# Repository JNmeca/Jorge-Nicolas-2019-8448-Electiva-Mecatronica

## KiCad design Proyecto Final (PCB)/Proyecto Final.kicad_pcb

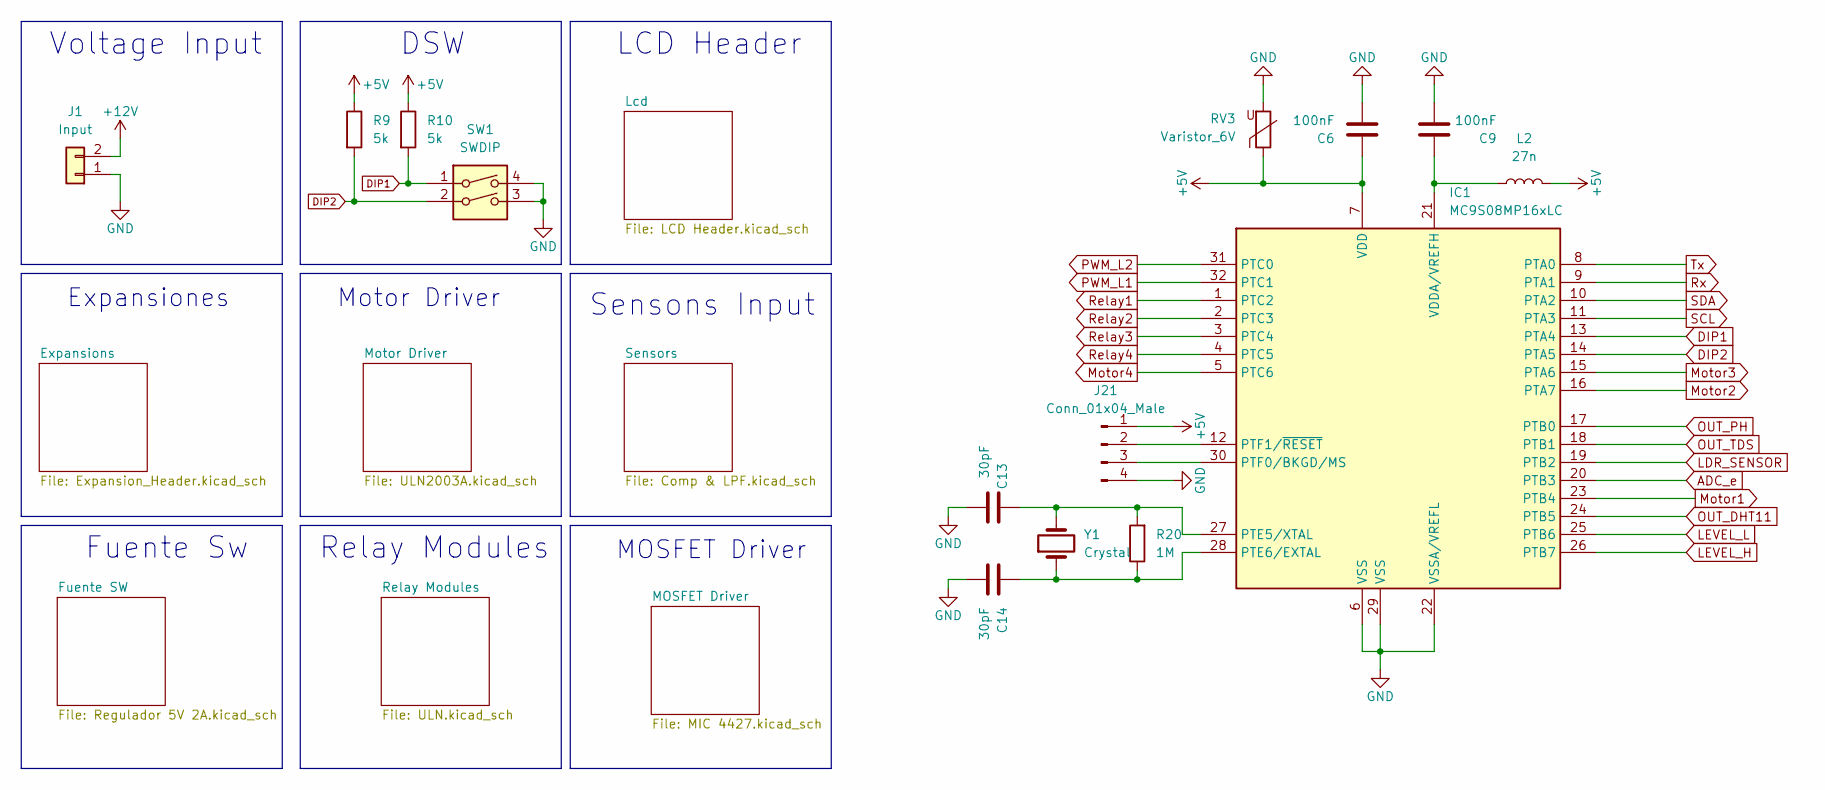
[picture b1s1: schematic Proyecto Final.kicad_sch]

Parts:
C6, C9: 100nF; C_0603_1608Metric
C13, C14: 30pF; C_0603_1608Metric
IC1: MC9S08MP16xLC; LQFP-32_7x7mm_P0.8mm
J1: Input; TerminalBlock_bornier-2_P5.08mm
J21: Conn_01x04_Male; PinHeader_1x04_P2.54mm_Vertical
L2: 27n; L_0805_2012Metric
R9, R10: 5k; R_0603_1608Metric
R20: 1M; R_0201_0603Metric
RV3: Varistor_6V; C_0805_2012Metric
SW1: SWDIP; SW_DIP_SPSTx02_Slide_9.78x7.26mm_W7.62mm_P2.54mm
Y1: Crystal; Crystal_HC49-4H_Vertical

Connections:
+5V: C6.2, IC1.7 (VDD), J21.1, L2.2, R9.1, R10.1, RV3.1; also elsewhere on the board
+12V: J1.2; also elsewhere on the board
ADC_e: IC1.20 (PTB3); also elsewhere on the board
DIP1: IC1.13 (PTA4), R10.2, SW1.1
DIP2: IC1.14 (PTA5), R9.2, SW1.2
GND: C6.1, C9.1, C13.1, C14.1, IC1.6 (VSS), IC1.22 (VSSA/VREFL), IC1.29 (VSS), J1.1, J21.4, RV3.2, SW1.3, SW1.4; also elsewhere on the board
LDR_SENSOR: IC1.19 (PTB2); also elsewhere on the board
LEVEL_H: IC1.26 (PTB7); also elsewhere on the board
LEVEL_L: IC1.25 (PTB6); also elsewhere on the board
Motor1: IC1.23 (PTB4); also elsewhere on the board
Motor2: IC1.16 (PTA7); also elsewhere on the board
Motor3: IC1.15 (PTA6); also elsewhere on the board
Motor4: IC1.5 (PTC6); also elsewhere on the board
unnamed: C9.2, IC1.21 (VDDA/VREFH), L2.1
unnamed: C13.2, IC1.27 (PTE5/XTAL), R20.2, Y1.2
unnamed: C14.2, IC1.28 (PTE6/EXTAL), R20.1, Y1.1
unnamed: IC1.12 (PTF1/~RESET), J21.2
unnamed: IC1.30 (PTF0/BKGD/MS), J21.3
OUT_DHT11: IC1.24 (PTB5); also elsewhere on the board
OUT_PH: IC1.17 (PTB0); also elsewhere on the board
OUT_TDS: IC1.18 (PTB1); also elsewhere on the board
PWM_L1: IC1.32 (PTC1); also elsewhere on the board
PWM_L2: IC1.31 (PTC0); also elsewhere on the board
Relay1: IC1.1 (PTC2); also elsewhere on the board
Relay2: IC1.2 (PTC3); also elsewhere on the board
Relay3: IC1.3 (PTC4); also elsewhere on the board
Relay4: IC1.4 (PTC5); also elsewhere on the board
Rx: IC1.9 (PTA1); also elsewhere on the board
SCL: IC1.11 (PTA3); also elsewhere on the board
SDA: IC1.10 (PTA2); also elsewhere on the board
Tx: IC1.8 (PTA0); also elsewhere on the board

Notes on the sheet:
DSW
Expansiones
LCD Header
Motor Driver
MOSFET Driver
Voltage Input
Sensons Input
Fuente Sw
Relay Modules

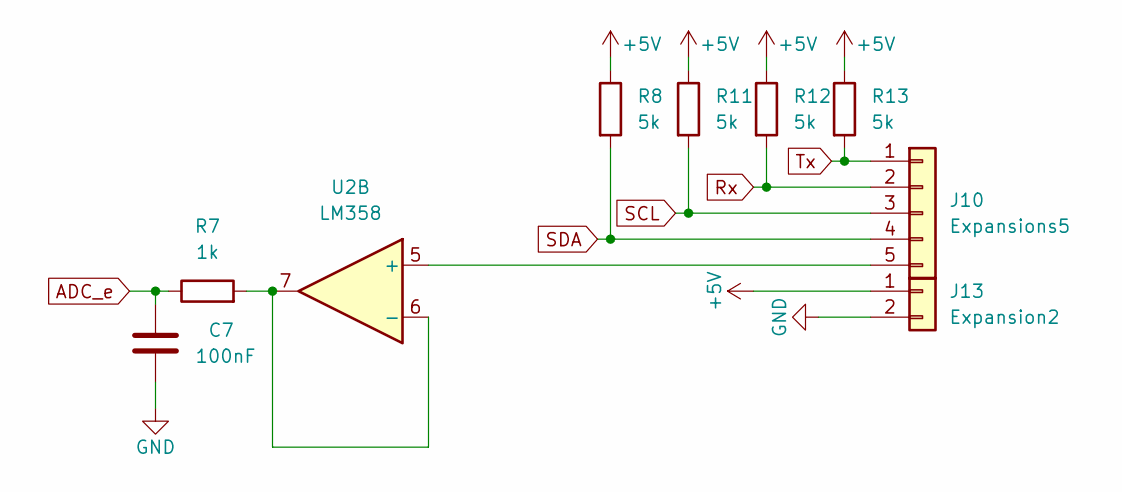
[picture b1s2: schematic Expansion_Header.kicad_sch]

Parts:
C7: 100nF; C_0603_1608Metric
J10: Expansions5; TerminalBlock_bornier-5_P5.08mm
J13: Expansion2; TerminalBlock_bornier-2_P5.08mm
R7: 1k; R_0603_1608Metric
R8, R11, R12, R13: 5k; R_0603_1608Metric
U2: LM358; SOIC-8_3.9x4.9mm_P1.27mm

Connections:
+5V: J13.1, R8.1, R11.1, R12.1, R13.1; also elsewhere on the board
ADC_e: C7.1, R7.1; also elsewhere on the board
GND: C7.2, J13.2; also elsewhere on the board
unnamed 41: J10.5, U2.5 (+); also elsewhere on the board
unnamed: R7.2, U2.6 (-), U2.7
Rx: J10.2, R12.2; also elsewhere on the board
SCL: J10.3, R11.2; also elsewhere on the board
SDA: J10.4, R8.2; also elsewhere on the board
Tx: J10.1, R13.2; also elsewhere on the board

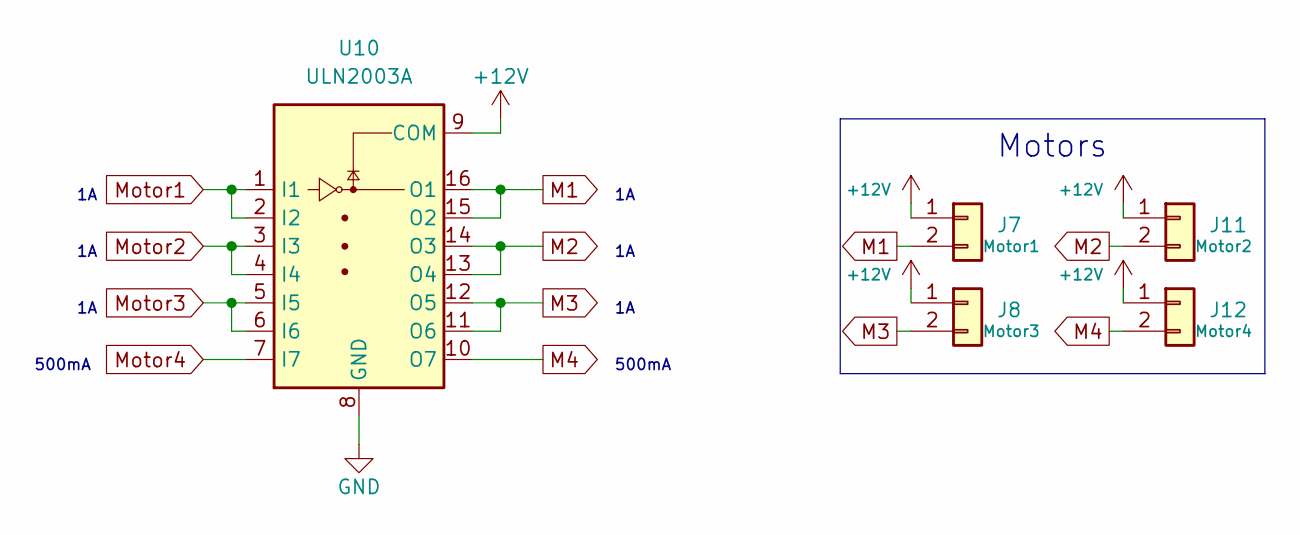
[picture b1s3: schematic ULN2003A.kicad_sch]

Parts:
J7: Motor1; TerminalBlock_bornier-2_P5.08mm
J8: Motor3; TerminalBlock_bornier-2_P5.08mm
J11: Motor2; TerminalBlock_bornier-2_P5.08mm
J12: Motor4; TerminalBlock_bornier-2_P5.08mm
U10: ULN2003A; SOIC-16_3.9x9.9mm_P1.27mm

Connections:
+12V: J7.1, J8.1, J11.1, J12.1, U10.9 (COM); also elsewhere on the board
GND: U10.8 (GND); also elsewhere on the board
M1: J7.2, U10.15 (O2), U10.16 (O1)
M2: J11.2, U10.13 (O4), U10.14 (O3)
M3: J8.2, U10.11 (O6), U10.12 (O5)
M4: J12.2, U10.10 (O7)
Motor1: U10.1 (I1), U10.2 (I2); also elsewhere on the board
Motor2: U10.3 (I3), U10.4 (I4); also elsewhere on the board
Motor3: U10.5 (I5), U10.6 (I6); also elsewhere on the board
Motor4: U10.7 (I7); also elsewhere on the board

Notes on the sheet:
500mA
Motors

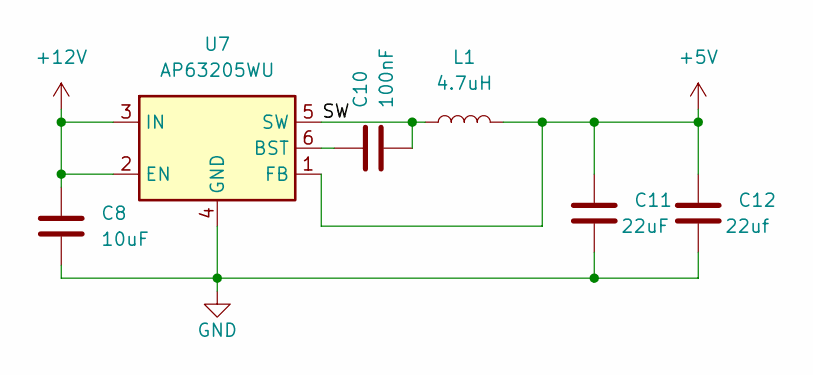
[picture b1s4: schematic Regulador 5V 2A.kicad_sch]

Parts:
C8: 10uF; C_0805_2012Metric
C10: 100nF; C_0201_0603Metric
C11: 22uF; C_0805_2012Metric
C12: 22uf; C_0805_2012Metric
L1: 4.7uH; L_Bourns_SRN6045TA
U7: AP63205WU; TSOT-23-6

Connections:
+5V: C11.1, C12.1, L1.2, U7.1 (FB); also elsewhere on the board
+12V: C8.1, U7.2 (EN), U7.3 (IN); also elsewhere on the board
/Fuente SW/SW: C10.1, L1.1, U7.5 (SW)
GND: C8.2, C11.2, C12.2, U7.4 (GND); also elsewhere on the board
unnamed: C10.2, U7.6 (BST)

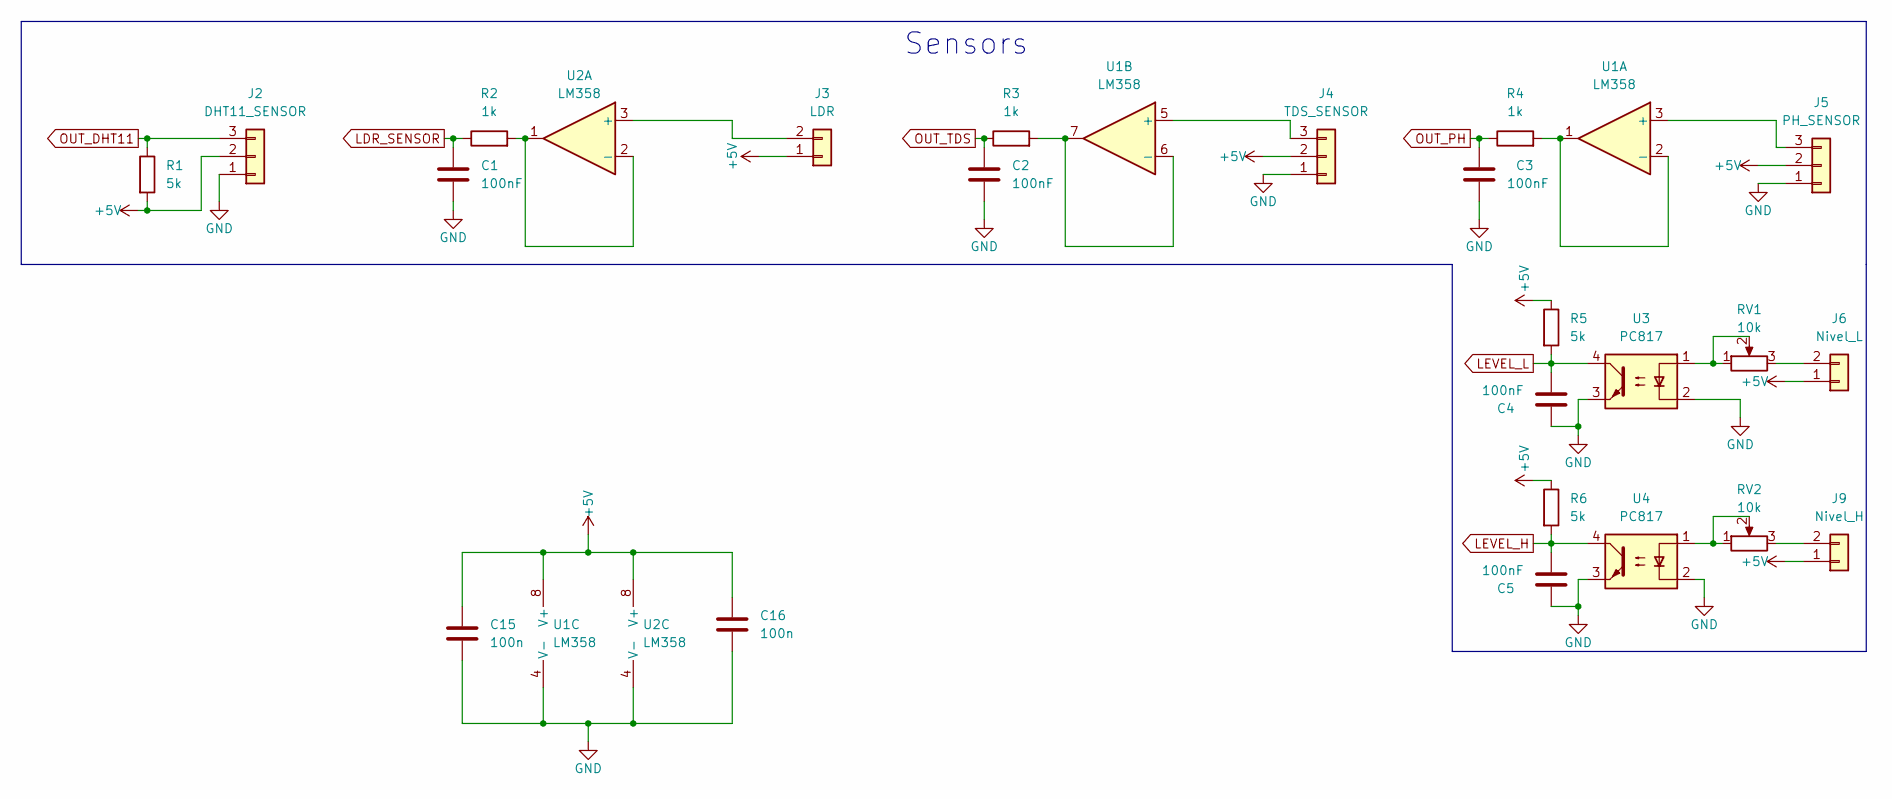
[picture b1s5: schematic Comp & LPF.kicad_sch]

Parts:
C1, C2, C3, C4, C5: 100nF; C_0603_1608Metric
C15, C16: 100n; C_0201_0603Metric
J2: DHT11_SENSOR; TerminalBlock_bornier-3_P5.08mm
J3: LDR; TerminalBlock_bornier-2_P5.08mm
J4: TDS_SENSOR; TerminalBlock_bornier-3_P5.08mm
J5: PH_SENSOR; TerminalBlock_bornier-3_P5.08mm
J6: Nivel_L; TerminalBlock_bornier-2_P5.08mm
J9: Nivel_H; TerminalBlock_bornier-2_P5.08mm
R1, R5, R6: 5k; R_0603_1608Metric
R2, R3, R4: 1k; R_0603_1608Metric
RV1, RV2: 10k; Potentiometer_Bourns_3266Y_Vertical
U1, U2: LM358; SOIC-8_3.9x4.9mm_P1.27mm
U3, U4: PC817; DIP-4_W7.62mm

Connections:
+5V: C15.1, C16.1, J2.2, J3.1, J4.2, J5.2, J6.1, J9.1, R1.2, R5.1, R6.1, U1.8 (V+), U2.8 (V+); also elsewhere on the board
GND: C1.2, C2.2, C3.2, C4.1, C5.1, C15.2, C16.2, J2.1, J4.1, J5.1, U1.4 (V-), U2.4 (V-), U3.2, U3.3, U4.2, U4.3; also elsewhere on the board
LDR_SENSOR: C1.1, R2.1; also elsewhere on the board
LEVEL_H: C5.2, R6.2, U4.4; also elsewhere on the board
LEVEL_L: C4.2, R5.2, U3.4; also elsewhere on the board
unnamed: J3.2, U2.3 (+)
unnamed: J4.3, U1.5 (+)
unnamed: J5.3, U1.3 (+)
unnamed: J6.2, RV1.3
unnamed: J9.2, RV2.3
unnamed: R2.2, U2.1, U2.2 (-)
unnamed: R3.2, U1.6 (-), U1.7
unnamed: R4.2, U1.1, U1.2 (-)
unnamed: RV1.1, RV1.2, U3.1
unnamed: RV2.1, RV2.2, U4.1
OUT_DHT11: J2.3, R1.1; also elsewhere on the board
OUT_PH: C3.1, R4.1; also elsewhere on the board
OUT_TDS: C2.1, R3.1; also elsewhere on the board

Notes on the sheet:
Sensors

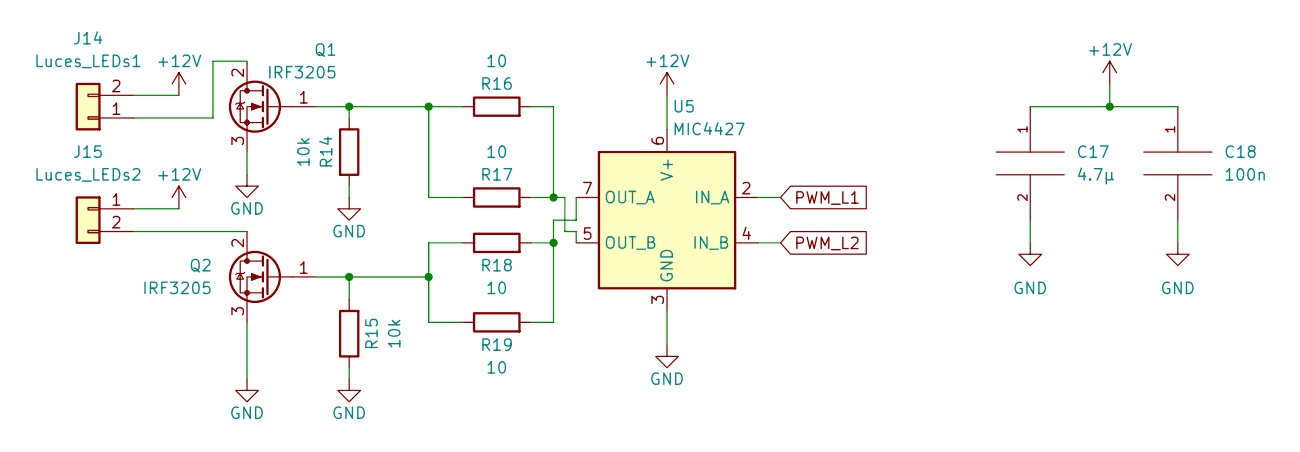
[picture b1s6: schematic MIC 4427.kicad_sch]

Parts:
C17: 4.7µ; C_0805_2012Metric
C18: 100n; C_0201_0603Metric
J14: Luces_LEDs1; TerminalBlock_bornier-2_P5.08mm
J15: Luces_LEDs2; TerminalBlock_bornier-2_P5.08mm
Q1, Q2: IRF3205; TO-220-3_Vertical
R14, R15: 10k; R_0603_1608Metric
R16, R17, R18, R19: 10; R_0603_1608Metric
U5: MIC4427; SOIC-8_3.9x4.9mm_P1.27mm

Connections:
+12V: C17.1, C18.1, J14.2, J15.1, U5.6 (V+); also elsewhere on the board
GND: C17.2, C18.2, Q1.3 (S), Q2.3 (S), R14.2, R15.1, U5.3 (GND); also elsewhere on the board
unnamed: J14.1, Q1.2 (D)
unnamed: J15.2, Q2.2 (D)
unnamed: Q1.1 (G), R14.1, R16.1, R17.1
unnamed: Q2.1 (G), R15.2, R18.1, R19.1
unnamed: R16.2, R17.2, U5.5 (OUT_B)
unnamed: R18.2, R19.2, U5.7 (OUT_A)
PWM_L1: U5.2 (IN_A); also elsewhere on the board
PWM_L2: U5.4 (IN_B); also elsewhere on the board

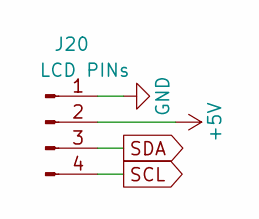
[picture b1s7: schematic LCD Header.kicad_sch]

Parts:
J20: LCD PINs; PinHeader_1x04_P2.54mm_Vertical

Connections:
+5V: J20.2; also elsewhere on the board
GND: J20.1; also elsewhere on the board
SCL: J20.4; also elsewhere on the board
SDA: J20.3; also elsewhere on the board

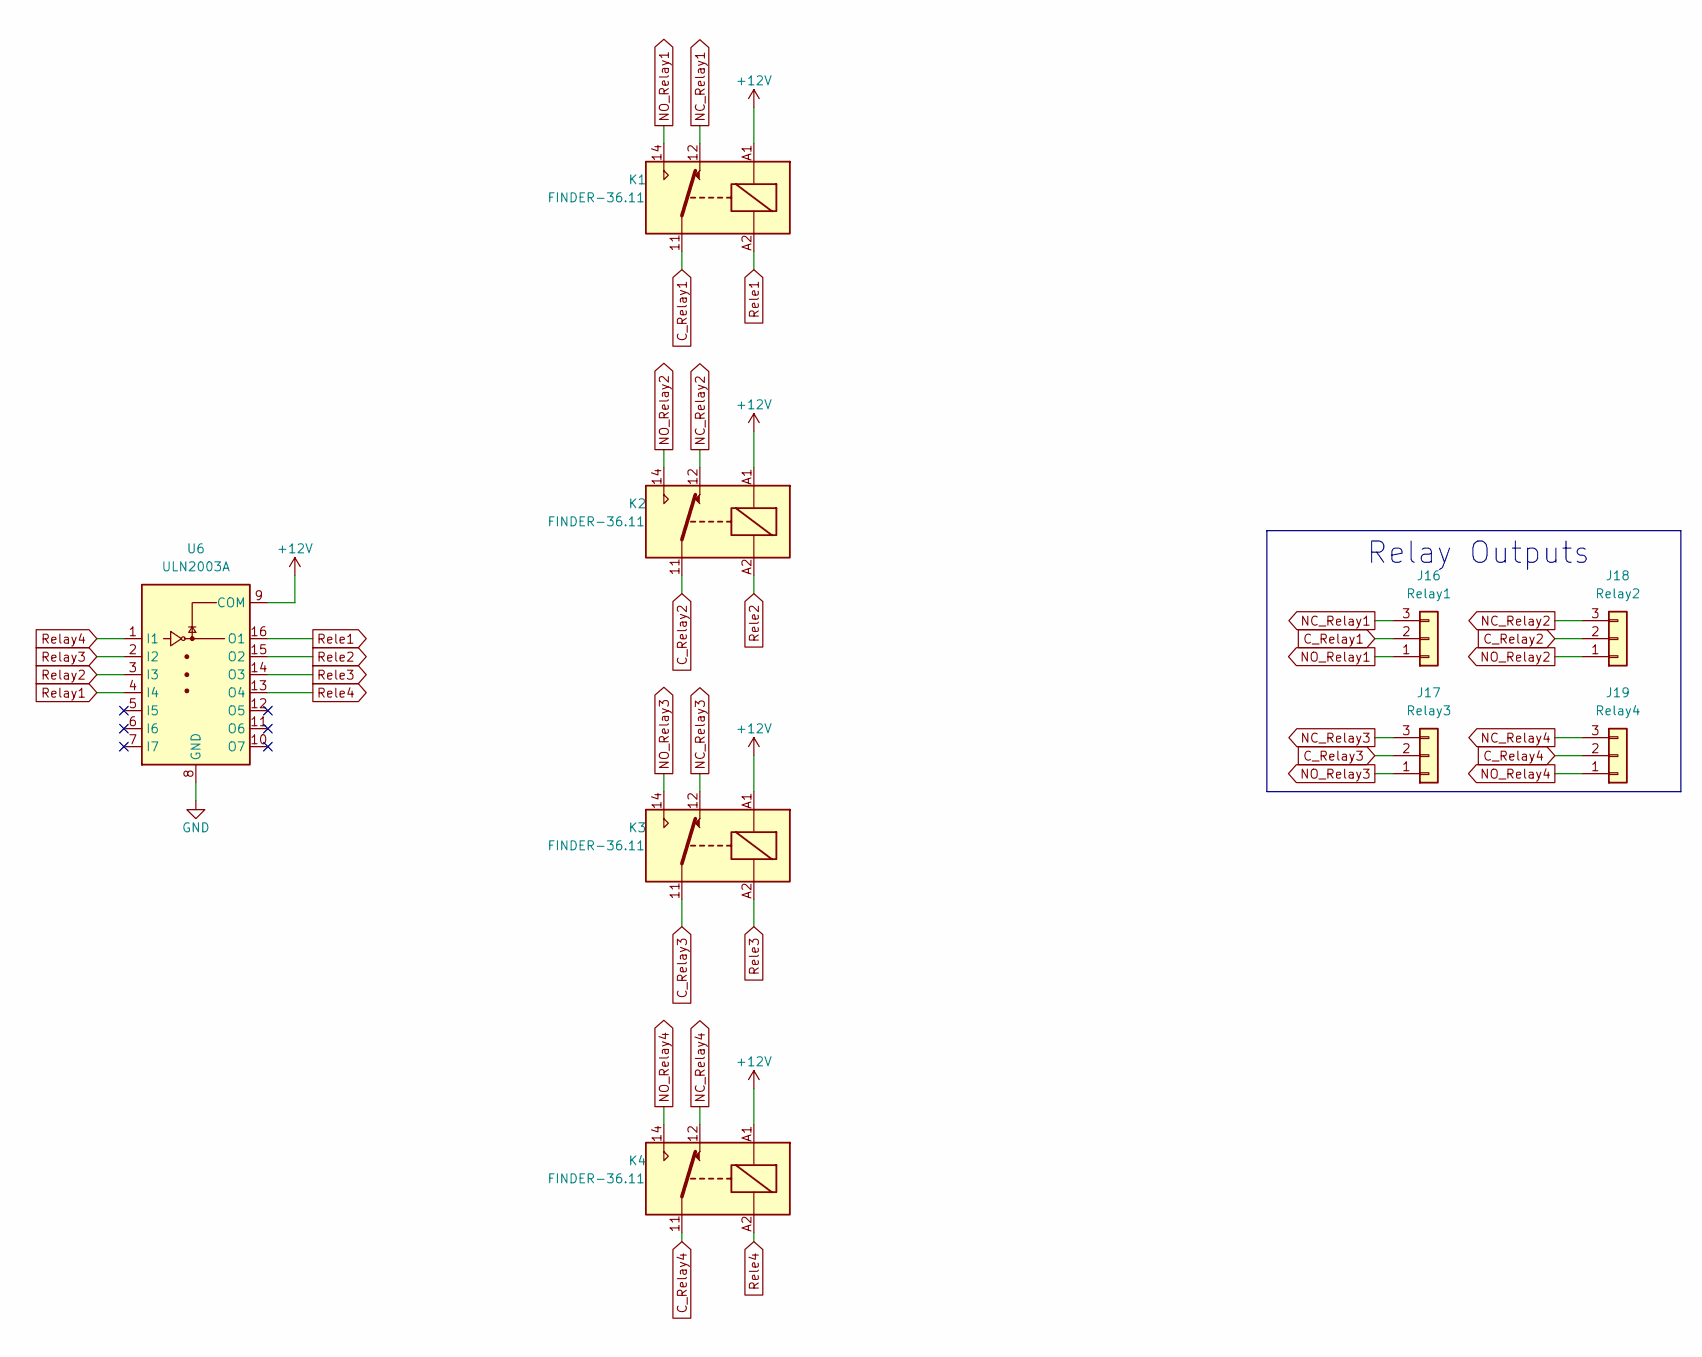
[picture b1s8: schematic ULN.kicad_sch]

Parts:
J16: Relay1; TerminalBlock_bornier-3_P5.08mm
J17: Relay3; TerminalBlock_bornier-3_P5.08mm
J18: Relay2; TerminalBlock_bornier-3_P5.08mm
J19: Relay4; TerminalBlock_bornier-3_P5.08mm
K1, K2, K3, K4: FINDER-36.11; Relay_SPDT_Finder_36.11
U6: ULN2003A; SOIC-16_3.9x9.9mm_P1.27mm

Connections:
+12V: K1.A1, K2.A1, K3.A1, K4.A1, U6.9 (COM); also elsewhere on the board
C_Relay1: J16.2, K1.11
C_Relay2: J18.2, K2.11
C_Relay3: J17.2, K3.11
C_Relay4: J19.2, K4.11
GND: U6.8 (GND); also elsewhere on the board
NC_Relay1: J16.3, K1.12
NC_Relay2: J18.3, K2.12
NC_Relay3: J17.3, K3.12
NC_Relay4: J19.3, K4.12
NO_Relay1: J16.1, K1.14
NO_Relay2: J18.1, K2.14
NO_Relay3: J17.1, K3.14
NO_Relay4: J19.1, K4.14
Relay1: U6.4 (I4); also elsewhere on the board
Relay2: U6.3 (I3); also elsewhere on the board
Relay3: U6.2 (I2); also elsewhere on the board
Relay4: U6.1 (I1); also elsewhere on the board
Rele1: K1.A2, U6.16 (O1)
Rele2: K2.A2, U6.15 (O2)
Rele3: K3.A2, U6.14 (O3)
Rele4: K4.A2, U6.13 (O4)

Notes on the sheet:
Relay Outputs

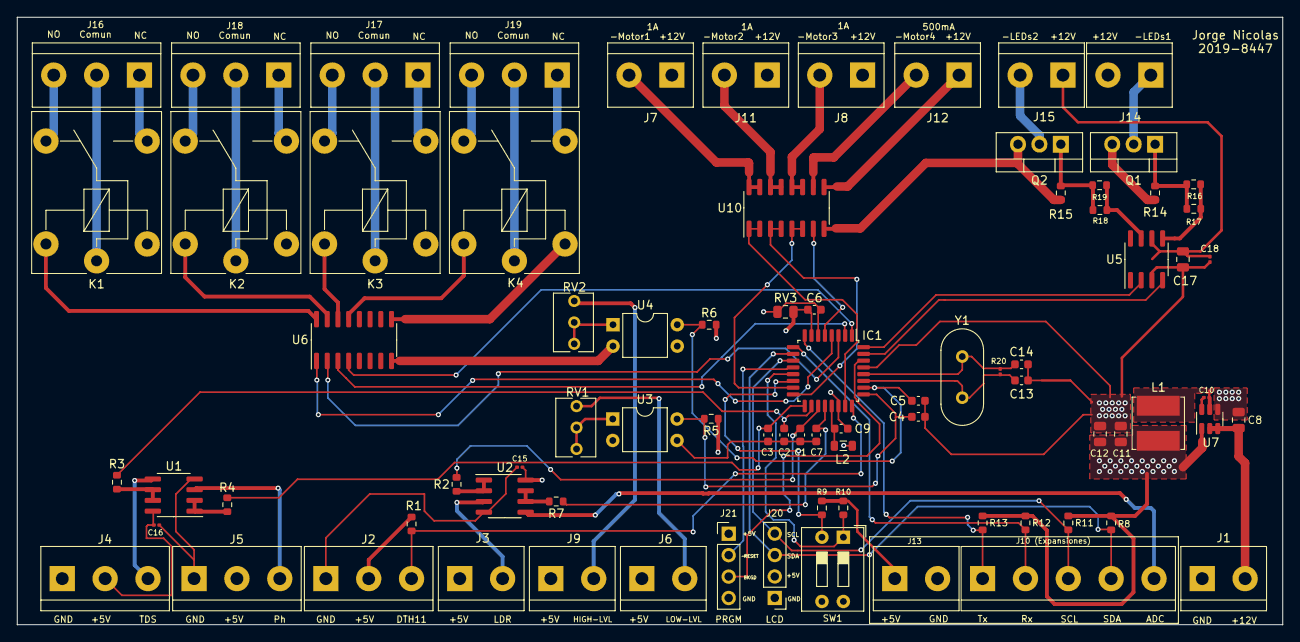
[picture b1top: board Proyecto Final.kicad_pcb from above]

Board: 4 copper layers, 150.0 x 72.0 mm, 81 parts (0 on the bottom side), 71 nets.

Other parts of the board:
J10 (Expansiones): Expansions5; TerminalBlock_bornier-5_P5.08mm

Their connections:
unnamed 41: J10 (Expansiones).5; also elsewhere on the board
Rx: J10 (Expansiones).2; also elsewhere on the board
SCL: J10 (Expansiones).3; also elsewhere on the board
SDA: J10 (Expansiones).4; also elsewhere on the board
Tx: J10 (Expansiones).1; also elsewhere on the board

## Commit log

2022-06-10 Entregas 10/06/2022
2022-06-17 Entrega 17/06/2022
2022-07-01 1/07//2022
2022-07-02 02/07/2022
2022-07-08 08/07/2022
2022-07-15 14/07/2022
2022-07-15 15/07/2022
2022-07-15 Corrección en el aula
2022-07-15 7 51
2022-07-22 22/07/2022
2022-07-22 22/07/2022 AULA
2022-07-22 5.02
2022-07-22 5.57
2022-07-22 6.28
2022-07-22 6.36
2022-07-22 7.07 PM
2022-07-24 18:12
2022-07-28 28-07-2022
2022-08-23 23/08/2022
2022-08-25 24/08/2022
2022-08-25 25/08/2022
2022-08-26 26/08/2022
